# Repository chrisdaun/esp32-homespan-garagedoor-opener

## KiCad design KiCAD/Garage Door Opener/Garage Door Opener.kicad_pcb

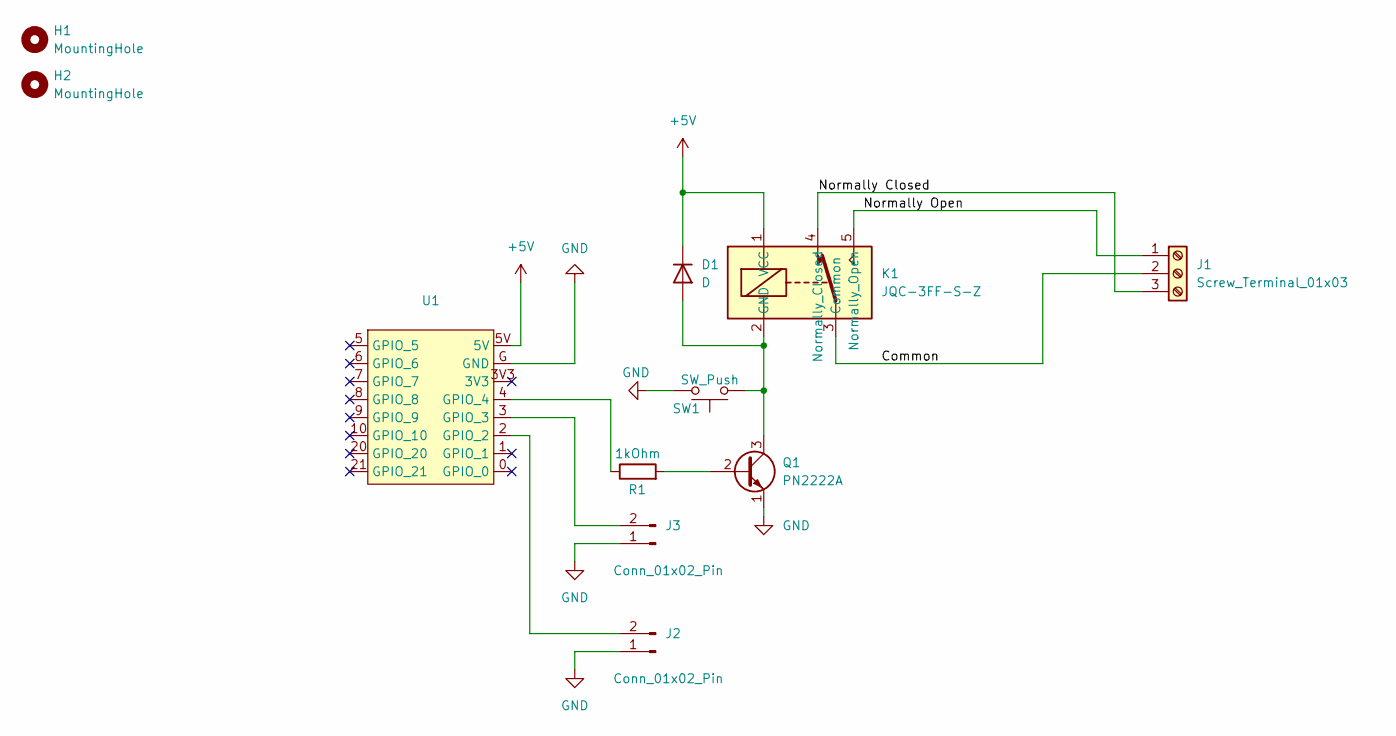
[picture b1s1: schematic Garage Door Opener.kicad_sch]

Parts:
D1: D; D_DO-35_SOD27_P7.62mm_Horizontal
H1, H2: MountingHole; MountingHole_3.5mm
J1: Screw_Terminal_01x03; TerminalBlock_Phoenix_MKDS-1,5-3_1x03_P5.00mm_Horizontal
J2, J3: Conn_01x02_Pin; PinHeader_1x02_P2.54mm_Vertical
K1: JQC-3FF-S-Z
Q1: PN2222A; TO-92_Inline
R1: 1kOhm; R_Axial_DIN0207_L6.3mm_D2.5mm_P7.62mm_Horizontal
SW1: SW_Push; SW_SPST_SKQG_WithStem
U1: ESP32-C3 Super Micro

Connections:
+5V: D1.1 (K), K1.1 (VCC), U1.5V
/Common: J1.2, K1.3 (Common)
/Normally Closed: J1.3, K1.4 (Normally_Closed)
/Normally Open: J1.1, K1.5 (Normally_Open)
GND: J2.1, J3.1, Q1.1 (E), SW1.2, U1.G (GND)
unnamed: D1.2 (A), K1.2 (GND), Q1.3 (C), SW1.1
unnamed: J2.2, U1.2 (GPIO_2)
unnamed: J3.2, U1.3 (GPIO_3)
unnamed: Q1.2 (B), R1.2
unnamed: R1.1, U1.4 (GPIO_4)

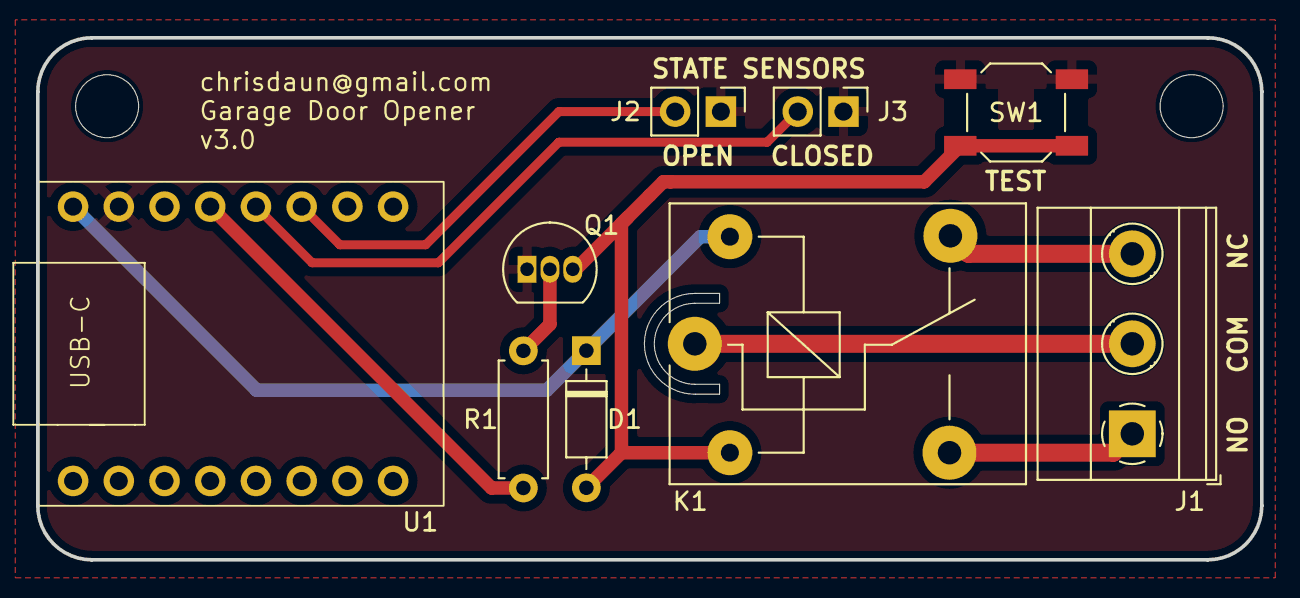
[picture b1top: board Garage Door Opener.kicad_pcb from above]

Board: 2 copper layers, 68.0 x 29.0 mm, 11 parts (0 on the bottom side), 10 nets.

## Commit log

2024-11-05 Adding custom board design
2024-11-21 Updated board design
2024-12-02 Updated logic levels for the YD board being used
2024-12-02 Adding image and README.MD
